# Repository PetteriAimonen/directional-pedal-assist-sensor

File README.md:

Directional pedal assist sensor
===============================

This repository contains a simple design for pedal assist sensor that does
not require mounting a separate magnet disc to the pedal axle.

Instead, the motion of the chainring is detected using analog hall sensors
and a magnet positioned nearby.

## Goal

Electric assist bicycles use a pedal sensor to control motor activation.
When pedals spin, motor is active - when pedals stop, motor stops.
Actual assist level is controlled separately, by e.g. a handle, torque sensor or accelerometer.

Most common pedal sensor type uses a separate magnet disc, which can be annoying to mount.
The number of magnets on the disc also limit the sensitivity, requiring longer rotation of the cranks before the motor activates.

For bicycles with pedal-activated brakes, it is also important to sense the movement direction.

## Theory of operation

Any ferromagnetic object will distort the magnetic field lines in its vicinity.
Analog [Hall effect](https://en.wikipedia.org/wiki/Hall_effect) sensors are used to detect the passing of the teeth by sensing the variations in the field.

The measured values are processed to determine middle analog level and then binarized.
After that it can be treated as a [quadrature encoder signal](https://en.wikipedia.org/wiki/Incremental_encoder#Quadrature_outputs).

This is used to count the number of passing teeth and determine the direction.
After a few teeth in forward direction have passed, signal is sent to motor controller to activate it.
If teeth move in the reverse direction or no pulses are detected within a timeout, the output signal goes back low.

## Circuit and PCB

The circuit is based on ATtiny824 microcontroller and [DRV5053](https://www.ti.com/lit/ds/symlink/drv5053.pdf?ts=1696181784911&ref_url=https%253A%252F%252Fwww.google.com%252F) analog Hall sensors. The built-in ADC is used to read the analog signals.
To improve signal resolution, the DAC is used as a reference voltage and PGA provides 4x gain.

## Software

Software is built using platformio.

To compile, run `pio run`. You can use a USB serial adapter for programming with [pyupdi](https://github.com/mraardvark/pyupdi). Run `pio run -t upload` to program the microcontroller.

There are unit tests that can you can run on PC with `pio test -e native`.

The `main.c` file contains a few settings that can be customized.
By enabling `ENABLE_UART` and `DATA_DUMP` the raw sensor data is written out over 115200 bps UART connection in binary format.
This can then decoded and run through signal processing using `pio run -e native -t exec < testdata.bin`, which will dump out a CSV file.

## Mounting

Positioning is important for reliable operation. For me, it has worked best to have the hall sensors in line with the chainring teeth, and as close as possible.

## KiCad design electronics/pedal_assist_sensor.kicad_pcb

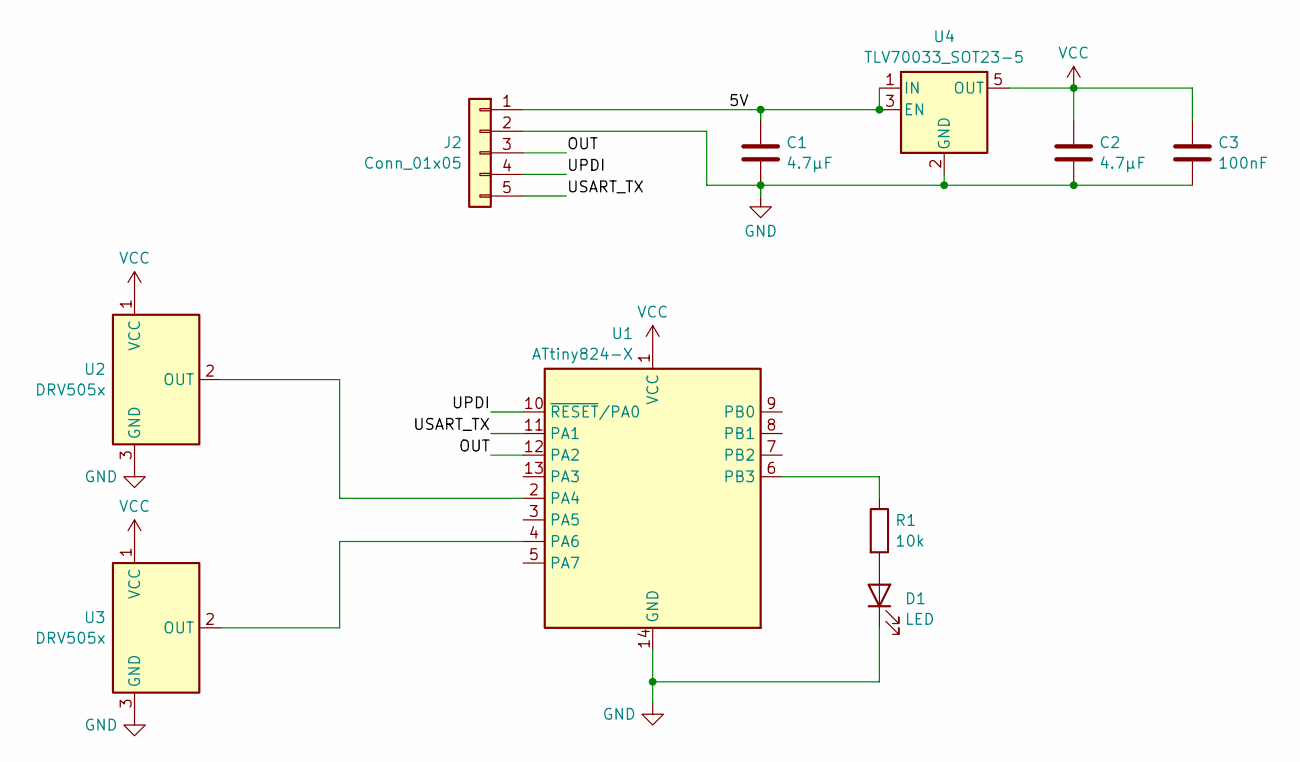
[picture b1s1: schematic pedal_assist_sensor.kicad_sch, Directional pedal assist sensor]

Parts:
C1, C2: 4.7µF; C_0603_1608Metric
C3: 100nF; C_0603_1608Metric
D1: LED; D_0603_1608Metric
J2: Conn_01x05; PinHeader_1x05_P2.54mm_Vertical
R1: 10k; R_0603_1608Metric
U1: ATtiny824-X; TSSOP-14_4.4x5mm_P0.65mm
U2, U3: DRV505x; SOT-23
U4: TLV70033_SOT23-5; SOT-23-5

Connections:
/5V: C1.1, J2.1, U4.1 (IN), U4.3 (EN)
/OUT: J2.3, U1.12 (PA2)
/UPDI: J2.4, U1.10 (~RESET/PA0)
/USART_TX: J2.5, U1.11 (PA1)
GND: C1.2, C2.2, C3.2, D1.1 (K), J2.2, U1.14 (GND), U2.3 (GND), U3.3 (GND), U4.2 (GND)
unnamed: D1.2 (A), R1.2
unnamed: U1.2 (PA4), U2.2 (OUT)
unnamed: U1.4 (PA6), U3.2 (OUT)
unnamed: R1.1, U1.6 (PB3)
VCC: C2.1, C3.1, U1.1 (VCC), U2.1 (VCC), U3.1 (VCC), U4.5 (OUT)

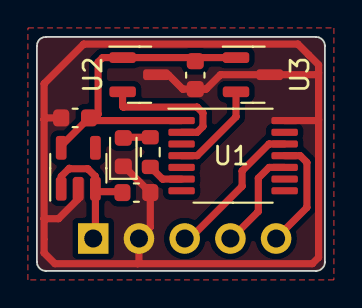
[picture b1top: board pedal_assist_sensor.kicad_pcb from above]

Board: 2 copper layers, 16.0 x 13.0 mm, 10 parts (1 on the bottom side), 10 nets.

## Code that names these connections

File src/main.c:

// This file implements a pedal assist sensor for e-bike use.
// It detects the chainring teeth using linear hall sensors (DRV5053)
// and a magnet.
//
// Pinout:
// PA4 / AIN4: First hall sensor analog signal
// PA6 / AIN6: Second hall sensor analog signal
// PB3:        LED
// PA1:        USART1 TX
// PA2:        Output signal
#define AIN_HALL0   4
#define AIN_HALL1   6
#define LED_PIN     3
#define USART_TX    1
#define OUT_PIN     2

// Detection parameters
// THRESHOLD:  Smaller value gives longer detection distance but is more sensitive to noise
// DECAY:      Smaller value makes min/max follower react faster to DC bias changes
// REVERSE:    Invert fwd/rev directions
// TICKS_FWD:  Minimum number of teeth in forward direction to enable the output
// TICKS_REV:  Minimum number of teeth in backward direction to disable the output
// TIMEOUT:    Time without detection to disable the output (milliseconds)
#define THRESHOLD   512
#define DECAY       10
#define MAXTIME     500
#define MINTIME     10
#define REVERSE     1
#define TICKS_FWD   4
#define TICKS_REV   2
#define TIMEOUT     1000

// IO parameters
// ENABLE_UART: Enable UART output on TX/PA1 pin (if disabled, outputs same as PA2)
// DATA_DUMP:   Instead of gear detection, just dump raw ADC data to UART TX pin
#define ENABLE_UART     0
#define DATA_DUMP       0

#include <avr/io.h>
#include <util/delay.h>
#include "gear_sensor.h"
#include <stdio.h>
#include <stdbool.h>

void setup()
{
    // Set clock to 10 MHz (maximum for 3.3V supply)
    CPU_CCP = CCP_IOREG_gc;
    CLKCTRL.MCLKCTRLB = 0x01;

    // Enable slew rate limitation (reduces noise)
    PORTA.PORTCTRL = PORT_SRL_bm;
    PORTB.PORTCTRL = PORT_SRL_bm;

    // Enable TX and OUT pins
    PORTA.DIR = (1 << USART_TX) | (1 << OUT_PIN);

    // Enable LED output
    PORTB.DIR = (1 << LED_PIN);

#if ENABLE_UART || DATA_DUMP
    // Enable USART1 at 115200 bps
    USART1.BAUD = (64L * F_CPU) / (16 * 115200L);
    USART1.CTRLC = USART_CHSIZE_8BIT_gc;
    USART1.CTRLB = USART_TXEN_bm;
#endif

    // Enable DACREF for subtracting the static magnetic field
    VREF.CTRLA = VREF_AC0REFSEL_2V5_gc;
    VREF.CTRLB = VREF_ADC0REFEN_bm | VREF_AC0REFEN_bm;
    AC0.DACREF = 100;

    // Enable ADC
    // Vref: internal 1.024 V
    // ADCCLK: 2.5 MHz
    // Averaging: 16 samples
    // PGA: enabled, 4x gain
    // PGA negative: DACREF
    ADC0.CTRLA = ADC_ENABLE_bm;
    ADC0.CTRLB = ADC_PRESC_DIV4_gc;
    ADC0.CTRLC = ADC_REFSEL_1024MV_gc | ADC_TIMEBASE2_bm;
    ADC0.CTRLE = 10;
    ADC0.CTRLF = ADC_LEFTADJ_bm | ADC_SAMPNUM_ACC16_gc;
    ADC0.PGACTRL = ADC_GAIN_4X_gc | ADC_PGABIASSEL_1_2X_gc | ADC_ADCPGASAMPDUR_20CLK_gc | ADC_PGAEN_bm;
    ADC0.MUXNEG = ADC_VIA_PGA_gc | ADC_MUXNEG_DACREF0_gc;
    ADC0.COMMAND = ADC_DIFF_bm | ADC_MODE_BURST_SCALING_gc | ADC_START_MUXPOS_WRITE_gc;
}

// Read single ADC channel, with hardware oversampling
int16_t read_adc(int hall_idx)
{
    if (hall_idx == 0)
    {
        ADC0.MUXPOS = ADC_VIA_PGA_gc | AIN_HALL0;
    }
    else
    {
        ADC0.MUXPOS = ADC_VIA_PGA_gc | AIN_HALL1;
    }

    loop_until_bit_is_set(ADC0.INTFLAGS, ADC_RESRDY_bp);
    return (int16_t)ADC0.RESULT;
}

// Adjust PGA negative reference level to keep the signals in measurable range
void adjust_dc_bias(int16_t hall1, int16_t hall2)
{
    static uint8_t dacref = 100;
    if (hall1 > 16384 && hall2 > 16384 && dacref < 255) dacref++;
    if (hall1 < -16384 && hall2 < -16384 && dacref > 0) dacref--;
    AC0.DACREF = dacref;
}

// Continuously send data to serial port
// Format is 5 bytes: SYNC, SENSOR1_LSB, SENSOR1_MSB, SENSOR2_LSB, SENSOR2_MSB.
// Sync byte is always 0xAA. Values encoded as signed 16-bit little-endian.
void dump_data()
{
    uint8_t dacref = 128;

    while(true)
    {
        loop_until_bit_is_set(USART1.STATUS, USART_DREIF_bp);
        USART1.TXDATAL = 0xAA;

        uint16_t hall1 = (uint16_t)read_adc(0);
        loop_until_bit_is_set(USART1.STATUS, USART_DREIF_bp);
        USART1.TXDATAL = (hall1 & 0xFF);
        loop_until_bit_is_set(USART1.STATUS, USART_DREIF_bp);
        USART1.TXDATAL = (hall1 >> 8);

        uint16_t hall2 = (uint16_t)read_adc(1);
        loop_until_bit_is_set(USART1.STATUS, USART_DREIF_bp);
        USART1.TXDATAL = (hall2 & 0xFF);
        loop_until_bit_is_set(USART1.STATUS, USART_DREIF_bp);
        USART1.TXDATAL = (hall2 >> 8);

        adjust_dc_bias(hall1, hall2);
    }
}

int main()
{
    setup();

#if DATA_DUMP
    // Dump raw ADC data over serial port.
    // Use tests/process_dump.c to analyze.
    dump_data();
#endif

    gear_sensor_state_t state = {};
    uint16_t timeout = 0;
    int8_t steps = 0;
    bool output_active = false;

    state.threshold = THRESHOLD;
    state.decay_exp = DECAY;

    while (1)
    {
        // Read ADC values
        int16_t hall1 = read_adc(0);
        int16_t hall2 = read_adc(1);
        adjust_dc_bias(hall1, hall2);

        // Detect gear movement
        int8_t delta = gear_sensor_process(&state, hall1, hall2);

        // Option to reverse direction
        if (REVERSE) delta = -delta;

        // Threshold step count and control output value
        if (delta > 0)
        {
            if (timeout > TIMEOUT)
            {
                // If restarting after timeout, give some
                // time for steps to accumulate.
                timeout = 0;
            }

            // One step forward
            if (steps < TICKS_FWD)
            {
                steps += delta;
            }
            else
            {
                timeout = 0;
                output_active = true;
            }
        }
        else if (delta < 0)
        {
            // One step backward
            if (steps > TICKS_REV)
            {
                steps += delta;
            }
            else
            {
                output_active = false;
            }
        }
        else
        {
            // No steps, keep track of timeout
            if (timeout > TIMEOUT)
            {
                steps = 0;
                output_active = false;
            }
            else
            {
                timeout++;
            }
        }

#if ENABLE_UART
        // Send direction to UART
        if (delta > 0)
        {
            USART1.TXDATAL = 'F';
        }
        else if (delta < 0)
        {
            USART1.TXDATAL = 'R';
        }
#endif

        // Output state on OUT pin and on UART pin (unless UART takes it over)
        if (output_active)
        {
            PORTA.OUTSET = (1 << USART_TX) | (1 << OUT_PIN);
        }
        else
        {
            PORTA.OUTCLR = (1 << USART_TX) | (1 << OUT_PIN);
        }

        // Status indication on LED
        // Blinks for each detected edge, shows the output state
        bool led_state = output_active;
        if (delta != 0)
        {
            led_state = !led_state;
        }

        if (led_state)
            PORTB.OUTSET = (1 << LED_PIN);
        else
            PORTB.OUTCLR = (1 << LED_PIN);
    }
}

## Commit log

2023-10-01 Updates for publication, add images
